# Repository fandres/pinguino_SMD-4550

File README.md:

This repository is possibly outdated
Este Repositorio se probablemente se encuentra desactualizado

Repository migrated to https://gitlab.com/fandres323/pinguino_SMD-4550
Repositorio migrado a https://gitlab.com/fandres323/pinguino_SMD-4550

# Pinguino SMD 4550

PCB in surface mount of the Pinguino board based on the microcontroller PIC18F4550 

## BOM 
Reference | Qty | Value | Footprint | Package
----- | ---------- | -------- | -------- | --------
C1 C2  | 2 | 22uF | Capacitors_SMD:C_0805 | 0805
C4  | 1 | 220nF | Capacitors_SMD:C_0805 | 0805
C3  | 1 | 100nF | Capacitors_SMD:C_0805 | 0805
C5  | 1 | 10-100uF | Capacitors_Tantalum_SMD:TantalC_SizeB_EIA-3528_Wave | B 3528
D1  | 1 | Run_LED | LEDs:LED_0805 | 0805
D2  | 1 | Power_LED | LEDs:LED_0805 | 0805
P1  | 1 | uUSB | Connect:USB_Mini-B | USB Female mini B 
P2 - P37 | 2 | Socket_Strips:Socket_Strip_Straight_2x10 | Female SIL 10x2 Pin
R2  | 1 | 10k | Resistors_SMD:R_0805 | 0805
R1 R3  | 2 | 470 | Resistors_SMD:R_0805 | 0805
SW1  | 1 | Reset | Buttons_Switches_SMD:SW_SPST_REED_CT05-XXXX-G1 | Sw SMD 1181
U1  | 1 | PIC18(L)F4550-I/PT | Housings_QFP:TQFP-44_10x10mm_Pitch0.8mm | TQFP-44
Y1  | 1 | Crystal | Crystal SMD:Crystal_SMD_5032_2Pads | 5032 2 Pads

# Order from OSH Park, $5 x3 

<a href="https://oshpark.com/shared_projects/KjakyOM4"></img></a>

# Pinguino IDE

http://pinguino.cc/download.php

# Images

# Attributions
<br /><span xmlns:dct="http://purl.org/dc/terms/" property="dct:title">Pinguino_SMD-4550</span> por <a xmlns:cc="http://creativecommons.org/ns#" href="https://github.com/fandres/pinguino_SMD-4550" property="cc:attributionName" rel="cc:attributionURL">Fabian Salamanca (fandres)</a> se distribuye bajo una <a rel="license" href="http://creativecommons.org/licenses/by-sa/4.0/">Licencia Creative Commons Atribución-CompartirIgual 4.0 Internacional</a>.<br />Basada en una obra en <a xmlns:dct="http://purl.org/dc/terms/" href="http://www.pinguino.cc/" rel="dct:source">http://www.pinguino.cc/</a>.

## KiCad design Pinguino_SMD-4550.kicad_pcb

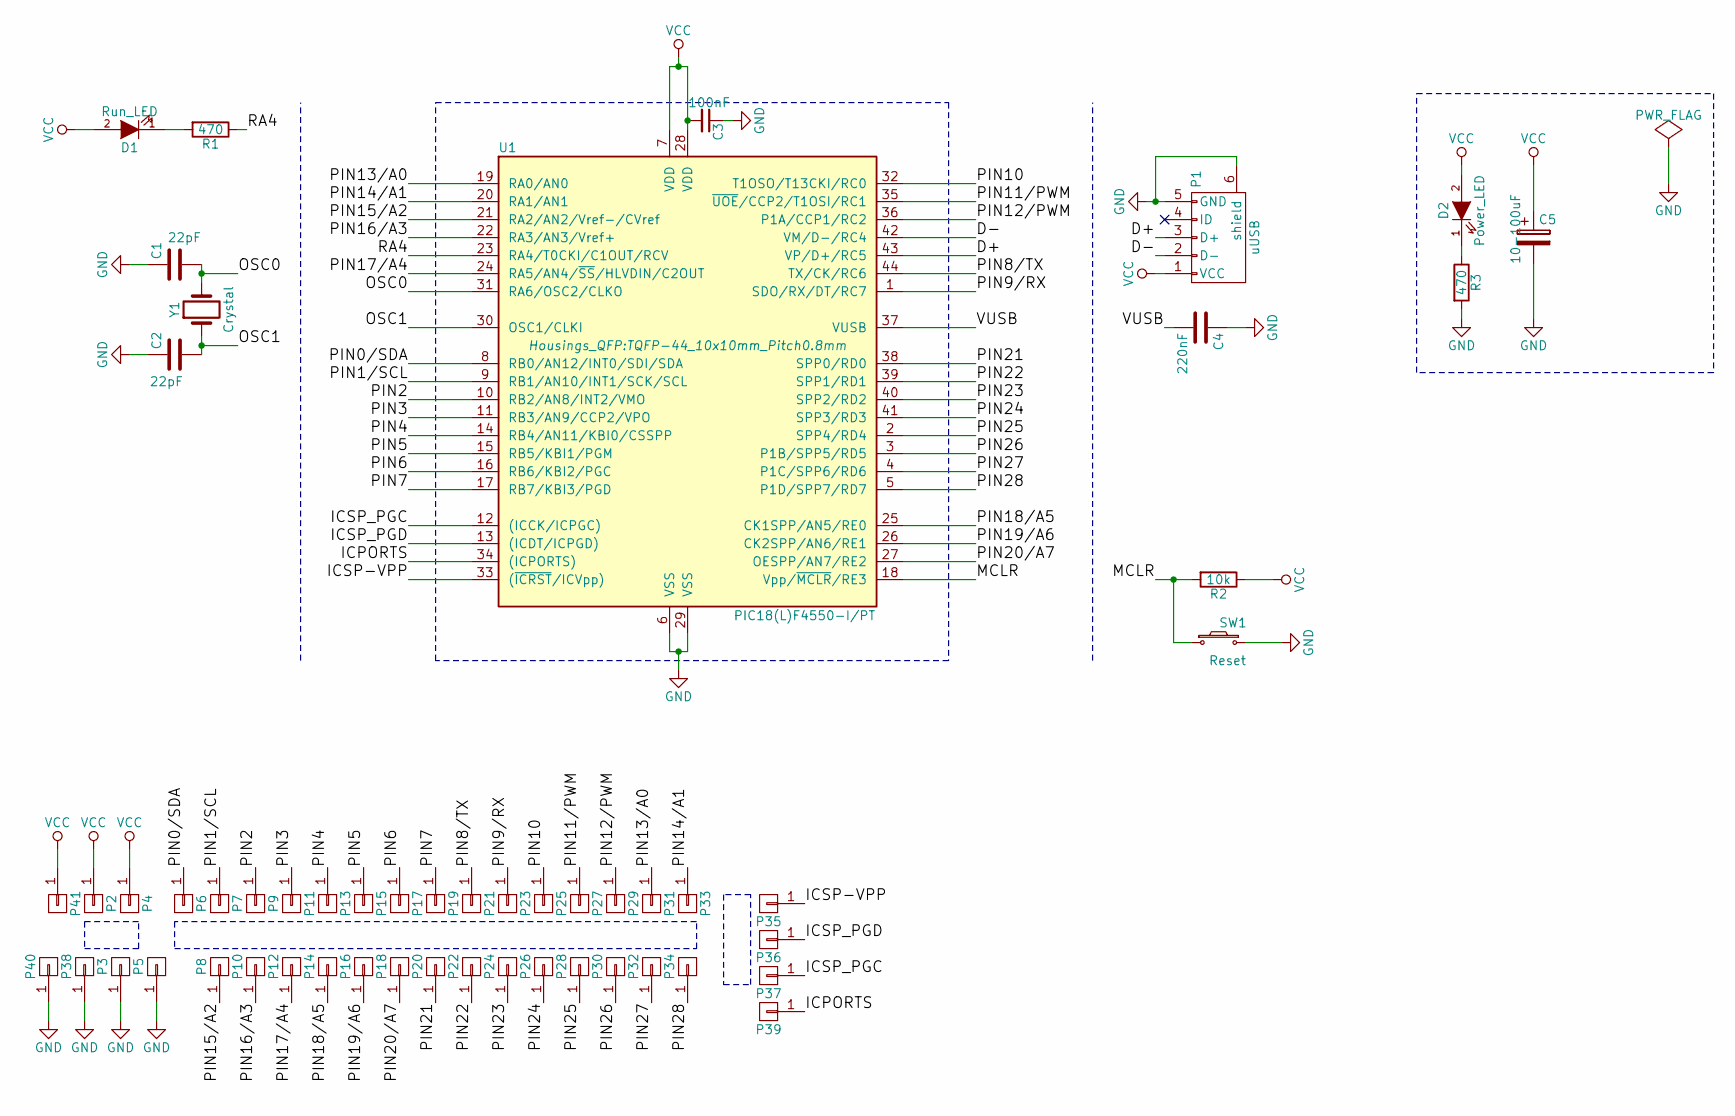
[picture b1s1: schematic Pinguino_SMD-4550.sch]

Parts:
C1, C2: 22pF; C_0805
C3: 100nF; C_0805
C4: 220nF; C_0805
C5: 10-100uF; CP_Tantalum_Case-B_EIA-3528-21_Reflow
D1: Run_LED; LED_0805
D2: Power_LED; LED_0805
P1: uUSB; USB_Mini-B
P2, P3, P4, P5, P6, P7, P8, P9, P10, P11, P12, P13, P14, P15, P16, P17, P18, P19, P20, P21, P22, P23, P24, P25, P26, P27, P28, P29, P30, P31, P32, P33, P34, P35, P36, P37, P38, P39, P40, P41: CONN_01X01; Socket_Strip_Straight_1x01
R1, R3: 470; R_0805
R2: 10k; R_0805
SW1: Reset; SW_SPST_REED_CT05-XXXX-G1
U1: PIC18(L)F4550-I/PT; TQFP-44_10x10mm_Pitch0.8mm
Y1: Crystal; Crystal_SMD_5032_2Pads

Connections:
/D+: P1.3 (D+), U1.43 (VP/D+/RC5)
/D-: P1.2 (D-), U1.42 (VM/D-/RC4)
/ICPORTS: P39.1, U1.34 ((ICPORTS))
/ICSP-VPP: P35.1, U1.33 ((~ICRST~/ICVpp))
/ICSP_PGC: P37.1, U1.12 ((ICCK/ICPGC))
/ICSP_PGD: P36.1, U1.13 ((ICDT/ICPGD))
/MCLR: R2.2, SW1.1, U1.18 (Vpp/~MCLR~/RE3)
/OSC0: C1.2, U1.31 (RA6/OSC2/CLKO), Y1.2
/OSC1: C2.2, U1.30 (OSC1/CLKI), Y1.1
/PIN0/SDA: P6.1, U1.8 (RB0/AN12/INT0/SDI/SDA)
/PIN1/SCL: P7.1, U1.9 (RB1/AN10/INT1/SCK/SCL)
/PIN2: P9.1, U1.10 (RB2/AN8/INT2/VMO)
/PIN3: P11.1, U1.11 (RB3/AN9/CCP2/VPO)
/PIN4: P13.1, U1.14 (RB4/AN11/KBI0/CSSPP)
/PIN5: P15.1, U1.15 (RB5/KBI1/PGM)
/PIN6: P17.1, U1.16 (RB6/KBI2/PGC)
/PIN7: P19.1, U1.17 (RB7/KBI3/PGD)
/PIN8/TX: P21.1, U1.44 (TX/CK/RC6)
/PIN9/RX: P23.1, U1.1 (SDO/RX/DT/RC7)
/PIN10: P25.1, U1.32 (T1OSO/T13CKI/RC0)
/PIN11/PWM: P27.1, U1.35 (~UOE~/CCP2/T1OSI/RC1)
/PIN12/PWM: P29.1, U1.36 (P1A/CCP1/RC2)
/PIN13/A0: P31.1, U1.19 (RA0/AN0)
/PIN14/A1: P33.1, U1.20 (RA1/AN1)
/PIN15/A2: P8.1, U1.21 (RA2/AN2/Vref-/CVref)
/PIN16/A3: P10.1, U1.22 (RA3/AN3/Vref+)
/PIN17/A4: P12.1, U1.24 (RA5/AN4/~SS~/HLVDIN/C2OUT)
/PIN18/A5: P14.1, U1.25 (CK1SPP/AN5/RE0)
/PIN19/A6: P16.1, U1.26 (CK2SPP/AN6/RE1)
/PIN20/A7: P18.1, U1.27 (OESPP/AN7/RE2)
/PIN21: P20.1, U1.38 (SPP0/RD0)
/PIN22: P22.1, U1.39 (SPP1/RD1)
/PIN23: P24.1, U1.40 (SPP2/RD2)
/PIN24: P26.1, U1.41 (SPP3/RD3)
/PIN25: P28.1, U1.2 (SPP4/RD4)
/PIN26: P30.1, U1.3 (P1B/SPP5/RD5)
/PIN27: P32.1, U1.4 (P1C/SPP6/RD6)
/PIN28: P34.1, U1.5 (P1D/SPP7/RD7)
/RA4: R1.1, U1.23 (RA4/T0CKI/C1OUT/RCV)
/VUSB: C4.2, U1.37 (VUSB)
GND: C1.1, C2.1, C3.1, C4.1, C5.2, P1.5 (GND), P1.6 (shield), P3.1, P5.1, P38.1, P40.1, R3.2, SW1.2, U1.6 (VSS), U1.29 (VSS)
unnamed: D1.1 (K), R1.2
unnamed: D2.1 (K), R3.1
VCC: C3.2, C5.1, D1.2 (A), D2.2 (A), P1.1 (VCC), P2.1, P4.1, P41.1, R2.1, U1.7 (VDD), U1.28 (VDD)

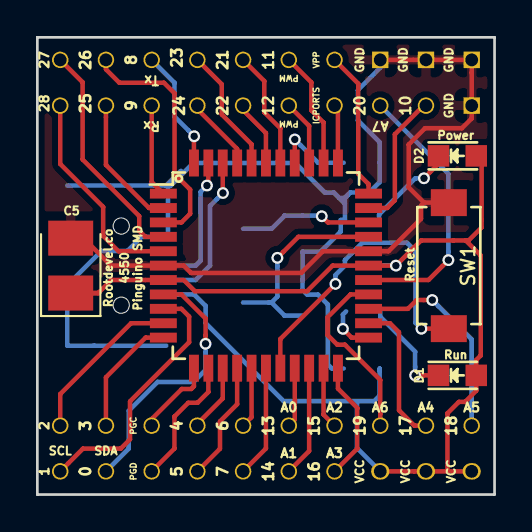
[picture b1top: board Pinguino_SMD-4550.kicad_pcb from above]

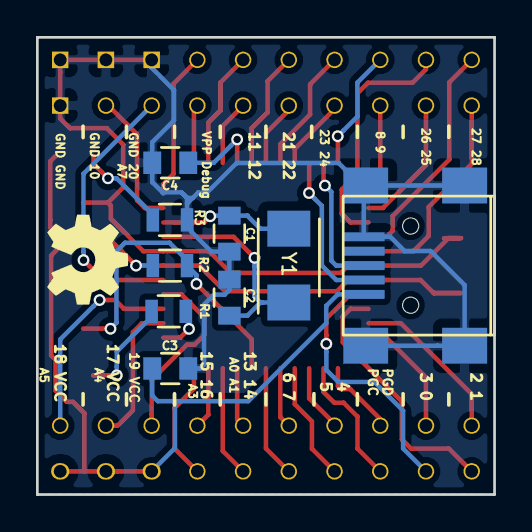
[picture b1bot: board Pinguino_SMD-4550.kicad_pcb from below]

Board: 2 copper layers, 25.4 x 25.4 mm, 54 parts (49 on the bottom side), 44 nets.

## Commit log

2016-12-22 Esquema + Componentes asociados (CvPcb)
2016-12-22 Upload Projec files; Esquema + Componentes asociados (CvPcb)
2016-12-28 Reorganized and aligned components. Capapol -> Tantalum B 3528.
2016-12-28 Autoruting
2016-12-29 Fixed error: VCC -> Pin 28, GND -> C3. Autoruting
2016-12-31 Tracks improvement
2016-12-31 Added zones (F.cu, B.cu)
2017-01-03 Silkscreen layers
2017-01-03 Added BOM and modified README.md
2017-01-03 Modified README.md, OSHPARK
2017-01-04 Model 3D: Board
2017-01-04 Fixed bug: STL
2017-01-05 Model 3D: Case
2017-01-05 Added image: Case
2017-01-05 Modified README.md
2017-02-22 Fixed Silkscreen and others. Modified readme.md file. Add Licence
2017-02-22 Reorganized and aligned components.
2017-02-22 Generate gerber
2017-02-22 Fixed info: capa-e
2017-02-22 Resized Throug Hole Pads
2017-02-22 Autoruting1, Reorganized Componets
2017-02-22 Autoruting2, Reorganized Componets
2017-02-22 Autoruting3
2017-02-22 Tracks and Vias improvement
2017-02-22 Added zones (F.cu, B.cu -> GND)
2017-02-23 Modified README.md file, Images, oshpark and components
2017-02-24 Model 3D: Case 4550
2017-02-27 Silkscreen layes: Logos
2017-04-09 F.Fab, B.Fab
2017-05-27 Bug Fixed: RA4
2017-05-28 Added image
2018-06-12 Update README.md
    Repository migrated to https://gitlab.com/fandres323/pinguino_SMD-4550
